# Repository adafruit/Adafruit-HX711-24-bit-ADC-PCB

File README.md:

## Adafruit HX711 24-bit ADC for Load Cells / Strain Gauges PCB

<a href="http://www.adafruit.com/products/5974"><br/>
Click here to purchase one from the Adafruit shop</a>

PCB files for the Adafruit HX711 24-bit ADC for Load Cells / Strain Gauges. 

Format is EagleCAD schematic and board layout
* https://www.adafruit.com/product/5974

### Description

If you are feeling the stress and strain of modern life a Wheatstone bridge and you want to quantify it, this handy breakout will do the job, no sweat! The Adafruit HX711 Breakout contains a super-high-resolution 24-Bit differential ADC with extra gain circuitry that makes it perfect for measuring strain gauges / load cells or other sensors that have four wires that are connected in a Wheatstone bridge arrangement.

Each breakout comes with a HX711 ADC chip, plus some support circuitry, and 6 port terminal block that can be used to connect one or two 4-wire sensors. The E- pad connects to ground (often a black wire), the E+ pad connects to the power voltage supplied to the HX711 (often a red wire).

Then A- and A+ pads connect to the differential outputs from the bridge. For example, connecting to a strain gauge these tend to be the white and green wires. If you have a second gauge or voltage you want to measure, you can use the B- and B+ pads. On the A channel, you can select 64x or 128x gain. On the B channel, you have a fixed 32x gain.

As the sensor is twisted and bent, the slight changes in resistance are converted to minuscule voltage changes that can be read by the HX711 ADC for converting into force or mass measurements. You can use our Arduino library or CedarGrove's CircuitPython/Python library to configure and read the ADC for fast interfacing. Note that this sensor has a fixed I2C address, if multiple sensors are desired on one I2C bus, a multiplexer can be used.

This sensor uses a two-wire protocol, similar to SPI. If you want a similar sensor but I2C, check out the NAU7802 breakout we make. We based this design on the excellent Sparkfun HX711 breakout: incorporating their split analog/digital supply and digital supply filtering. We then made a few tweaks: pre-soldered terminal blocks, the second bridge exposed, and a slide switch to change between 10 SPS and 80 SPS rates.

### License

Adafruit invests time and resources providing this open source design, please support Adafruit and open-source hardware by purchasing products from [Adafruit](https://www.adafruit.com)!

Designed by Limor Fried/Ladyada for Adafruit Industries.

Creative Commons Attribution/Share-Alike, all text above must be included in any redistribution. 
See license.txt for additional details.

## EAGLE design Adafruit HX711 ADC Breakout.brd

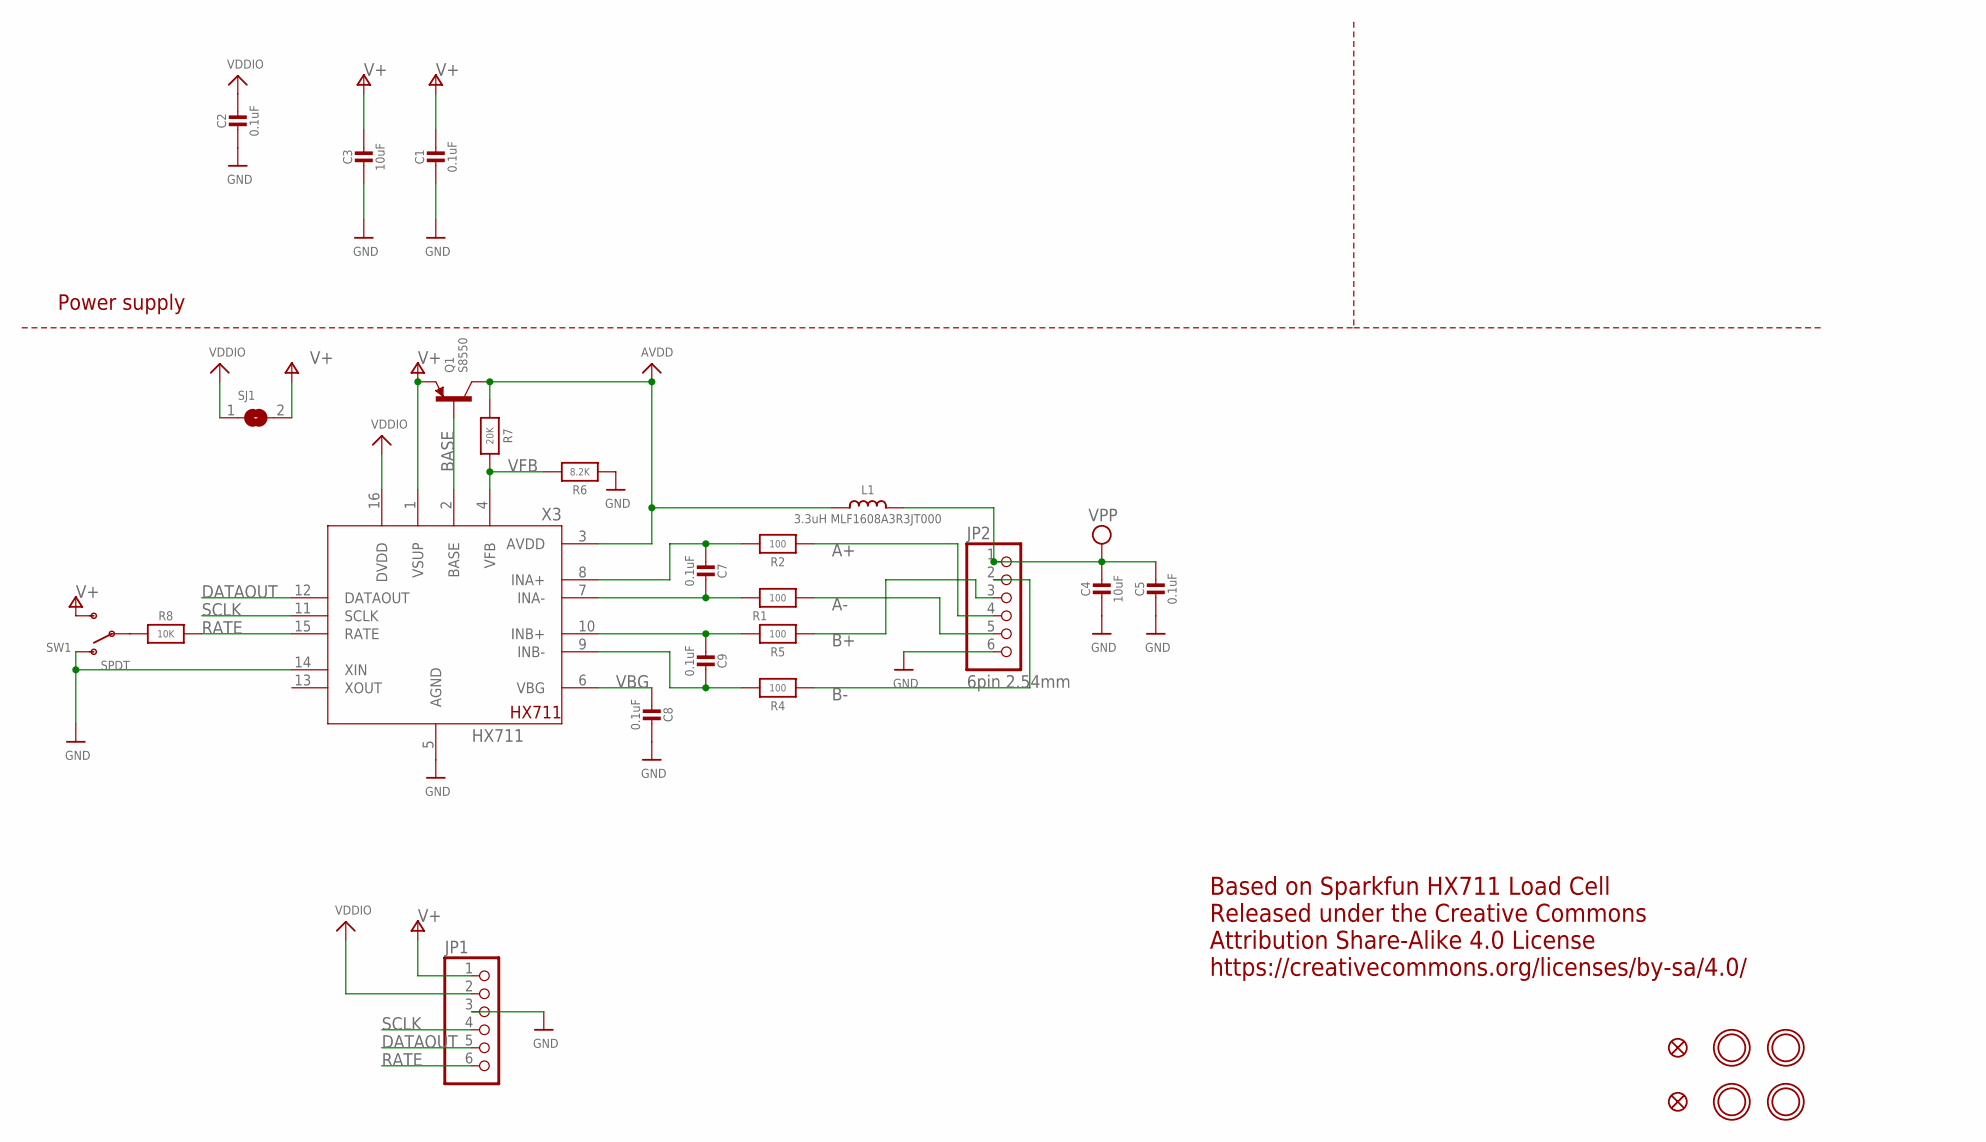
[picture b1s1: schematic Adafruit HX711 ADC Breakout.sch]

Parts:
C1, C2, C5, C7, C8, C9: 0.1uF; 0603-NO
C3, C4: 10uF; 0805-NO
FID3, FID4: FIDUCIAL_0.5MM
JP1: HEADER-1X670MIL; 1X06_ROUND_70
JP2: 6pin 2.54mm; 1X06_2.54MMTERMINAL
L1: 3.3uH MLF1608A3R3JT000; 0603-NO
Q1: S8550; SOT23-WIDE
R1, R2, R4, R5: 100; 0603-NO
R6: 8.2K; 0603-NO
R7: 20K; 0603-NO
R8: 10K; 0603-NO
SJ1: SOLDERJUMPER; SOLDERJUMPER_ARROW_NOPASTE
SW1: SPDT; SPDT_SMT_SSSS811101
U$1, U$17, U$19, U$21: MOUNTINGHOLE2.5; MOUNTINGHOLE_2.5_PLATED
X3: HX711; SO16

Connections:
A+: JP2.4, R2.2
A-: JP2.5, R1.2
AVDD: L1.1, Q1.3 (C), R7.2, X3.3 (AVDD)
B+: JP2.3, R5.2
B-: JP2.2, R4.2
BASE: Q1.1 (B), X3.2 (BASE)
DATAOUT: JP1.5, X3.12 (DATAOUT)
GND: C1.2, C2.2, C3.2, C4.2, C5.2, C8.1, JP1.3, JP2.6, R6.2, SW1.A (O), X3.5 (AGND), X3.14 (XIN)
unnamed: R8.2, SW1.B
unnamed: C7.1, R2.1, X3.8 (INA+)
unnamed: C7.2, R1.1, X3.7 (INA-)
unnamed: C9.1, R5.1, X3.10 (INB+)
unnamed: C9.2, R4.1, X3.9 (INB-)
RATE: JP1.6, R8.1, X3.15 (RATE)
SCLK: JP1.4, X3.11 (SCLK)
V+: C1.1, C3.1, JP1.1, Q1.2 (E), SJ1.2, SW1.C (S), X3.1 (VSUP)
VBG: C8.2, X3.6 (VBG)
VDDIO: C2.1, JP1.2, SJ1.1, X3.16 (DVDD)
VFB: R6.1, R7.1, X3.4 (VFB)
VPP: C4.1, C5.1, JP2.1, L1.2

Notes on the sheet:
Power supply
Based on Sparkfun HX711 Load Cell Released under the Creative Commons Attribution Share-Alike 4.0 License https://creativecommons.org/licenses/by-sa/4.0/

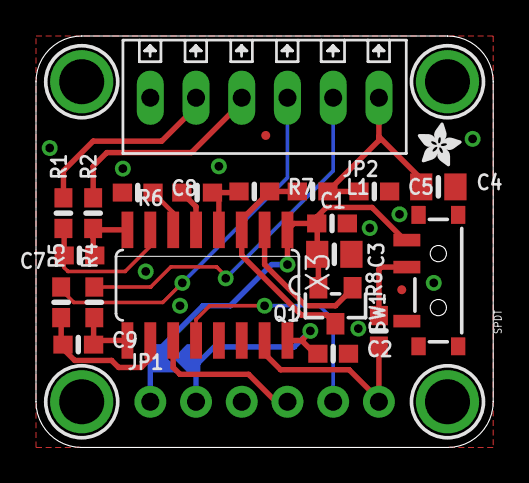
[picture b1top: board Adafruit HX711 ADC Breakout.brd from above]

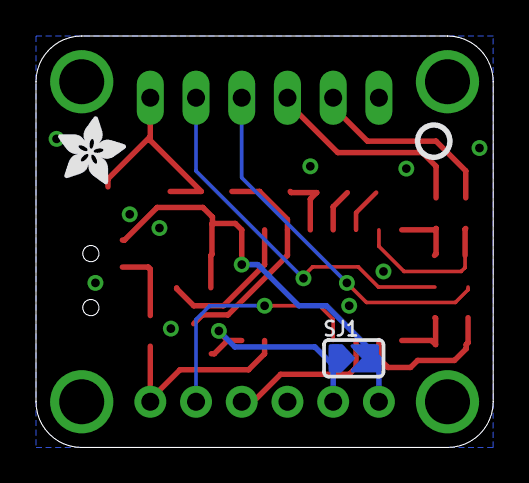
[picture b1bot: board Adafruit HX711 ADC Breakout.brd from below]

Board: 2 copper layers, 25.4 x 22.9 mm, 55 parts (11 on the bottom side), 20 nets.

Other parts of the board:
PLABEL0: PLABEL0
PLABEL1: PLABEL1
PLABEL2: PLABEL2
PLABEL3: PLABEL3
PLABEL4: PLABEL4
PLABEL5: PLABEL5
PLABEL6: PLABEL6
PLABEL7: PLABEL7
PLABEL8: PLABEL8
PLABEL9: PLABEL9
PLABEL10: PLABEL10
PLABEL11: PLABEL11
PLABEL12: PLABEL12
PLABEL13: PLABEL13
PLABEL14: PLABEL14
PLABEL15: PLABEL15
PLABEL16: PLABEL16
PLABEL17: PLABEL17
PLABEL18: PLABEL18
PLABEL19: PLABEL19
PLABEL20: PLABEL20
PLABEL21: PLABEL21
PLABEL22: PLABEL22
PLABEL23: PLABEL23
U$11: ADAFRUIT_2.5MM
U$22: ADAFRUIT_3.5MM
U$25: PCBFEAT-REV-040

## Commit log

2024-06-18 cookiecutter

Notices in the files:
parts and their libraries:
microbuilder: This work is placed in the public domain, and may be freely used for commercial and non-commercial work with the following conditions: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
